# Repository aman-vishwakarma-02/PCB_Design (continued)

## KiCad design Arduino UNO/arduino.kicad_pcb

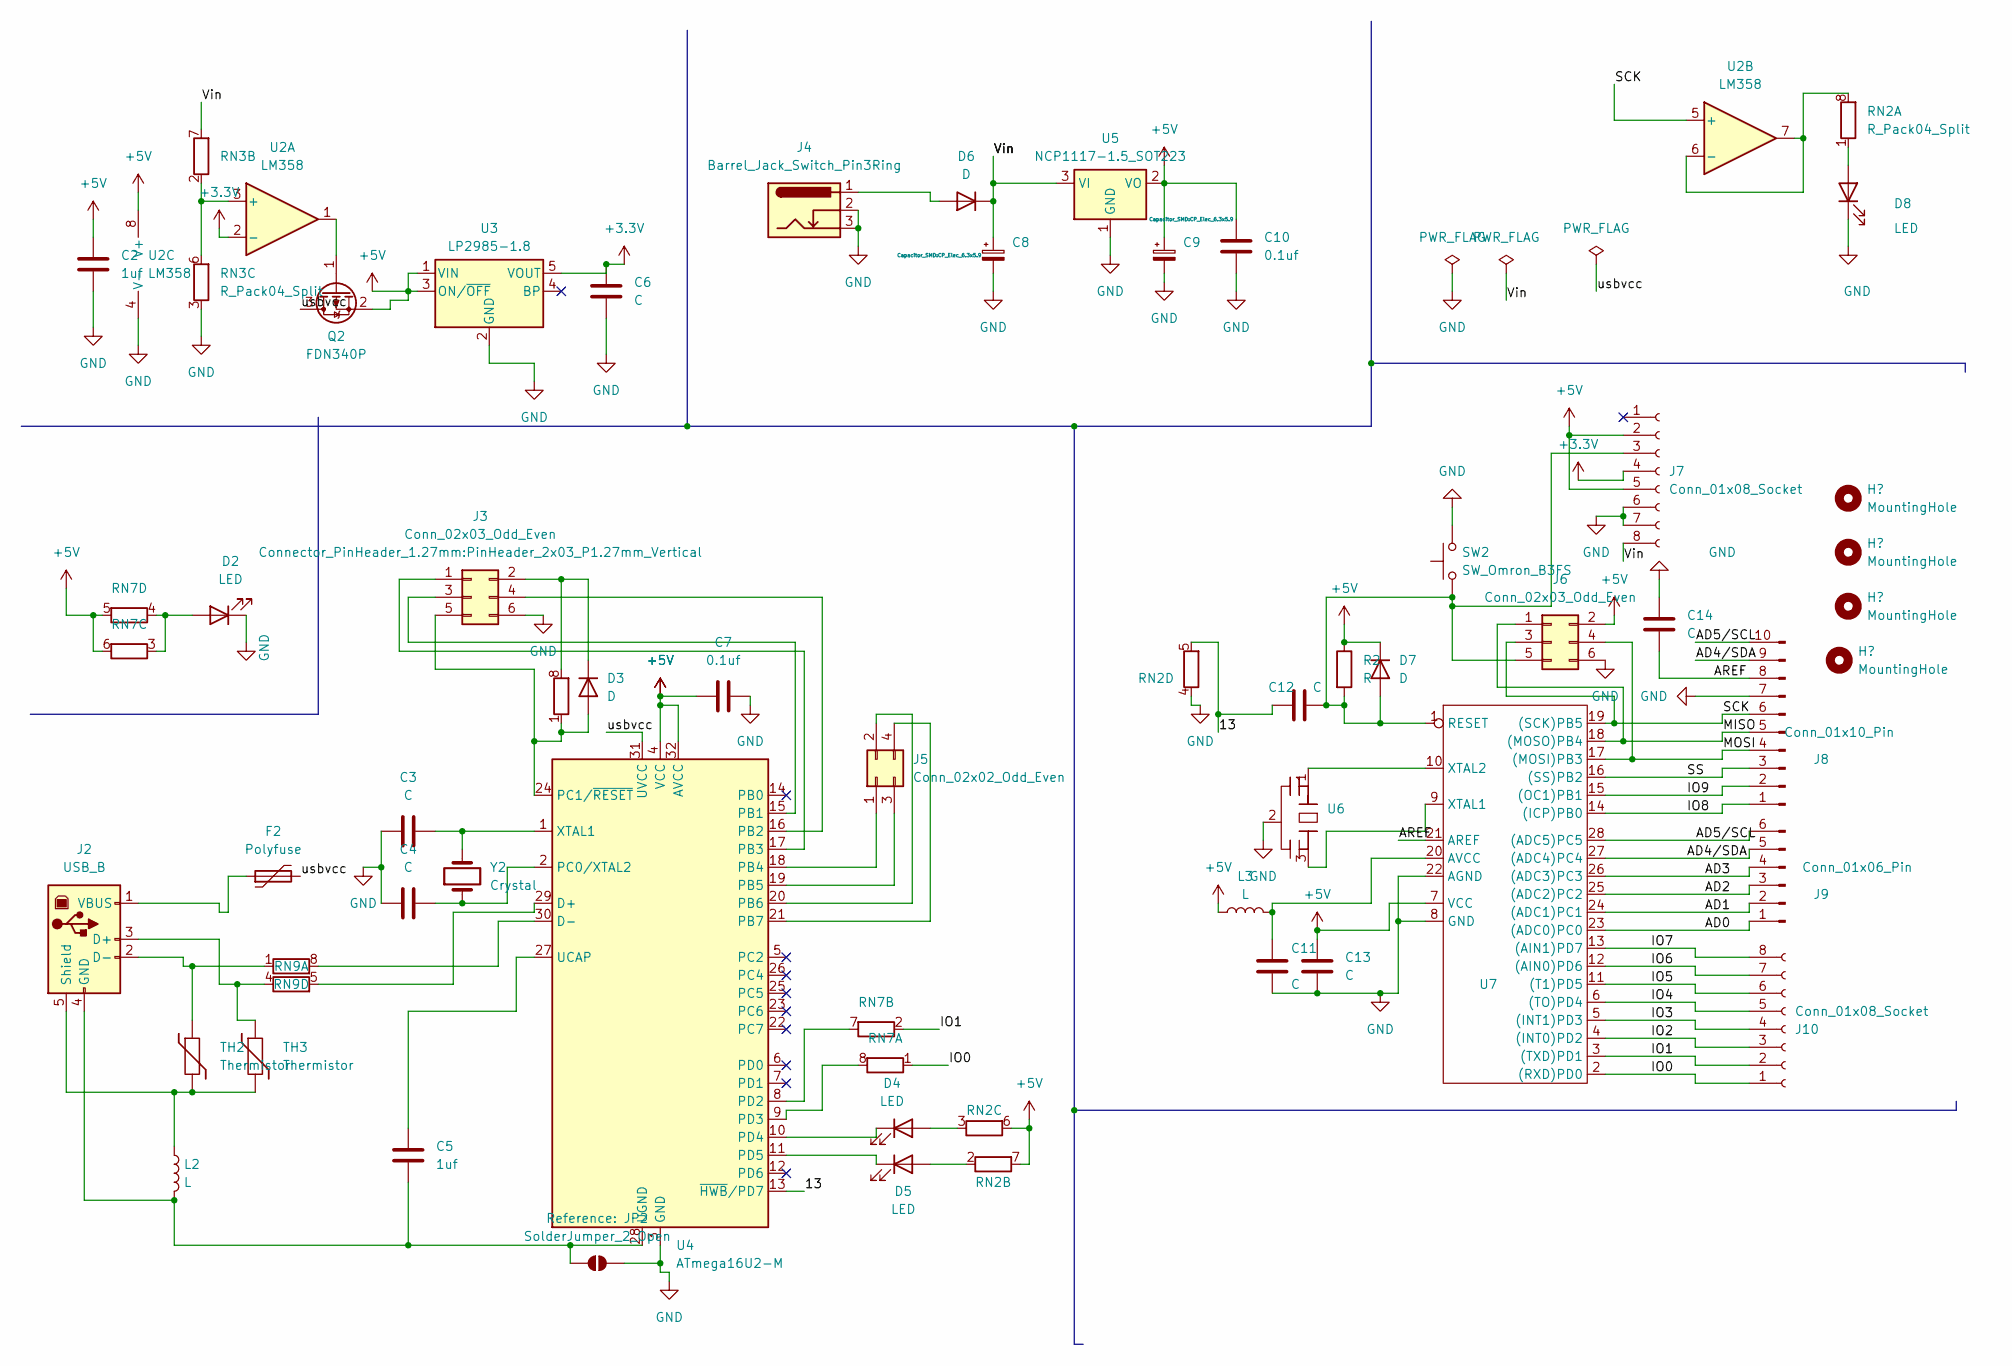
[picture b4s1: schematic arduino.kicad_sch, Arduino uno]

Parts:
C2, C5: 1uf; C_0603_1608Metric
C3, C4: C; C_0603_1608Metric_Pad1.08x0.95mm_HandSolder
C6: C; C_0805_2012Metric
C7, C10: 0.1uf; C_0603_1608Metric
C8, C9: C_Polarized_Small; CP_Elec_6.3x5.9
C11, C12, C13, C14: C; C_0603_1608Metric
D2, D4, D5: LED; LED_0402_1005Metric_Pad0.77x0.64mm_HandSolder
D3: D; D_0805_2012Metric_Pad1.15x1.40mm_HandSolder
D6: D; D_SOD-523
D7: D; D_1206_3216Metric_Pad1.42x1.75mm_HandSolder
D8: LED; LED_0603_1608Metric
F2: Polyfuse; R_1812_4532Metric
J2: USB_B; USB_B_OST_USB-B1HSxx_Horizontal
J3, J6: Conn_02x03_Odd_Even; PinHeader_2x03_P1.27mm_Vertical
J4: Barrel_Jack_Switch_Pin3Ring; BarrelJack_Wuerth_6941xx301002
J5: Conn_02x02_Odd_Even; PinHeader_2x02_P1.27mm_Vertical
J7, J10: Conn_01x08_Socket; PinSocket_1x08_P2.54mm_Vertical
J8: Conn_01x10_Pin; PinSocket_1x10_P2.54mm_Vertical
J9: Conn_01x06_Pin; PinSocket_1x06_P2.54mm_Vertical
JP2: SolderJumper_2_Open; SolderJumper-2_P1.3mm_Open_Pad1.0x1.5mm
L2: L; L_0603_1608Metric
L3: L; L_0805_2012Metric
Q2: FDN340P; SOT-23
R2: R; R_0603_1608Metric
RN2, RN9D2: R_Pack04_Split; R_Array_Convex_4x0402
RN3, RN7, RN9: R_Pack04_Split; R_Array_Concave_4x0402
SW2: SW_Omron_B3FS; SW_SPST_Omron_B3FS-100xP
TH2, TH3: Thermistor; R_0201_0603Metric
U2: LM358; SOIC-8_3.9x4.9mm_P1.27mm
U3: LP2985-1.8; SOT-23-5
U4: ATmega16U2-M; QFN-32-1EP_5x5mm_P0.5mm_EP3.3x3.3mm
U5: NCP1117-1.5_SOT223; SOT-223-3_TabPin2
U6: CSTCE16M0V53-R0
U7: DIP-28_W7.62mm_LongPads
Y2: Crystal; Crystal_HC49-4H_Vertical

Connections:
+3.3V: C6.1, J7.4, U2.2 (-), U3.5 (VOUT)
+5V: C2.2, C7.1, C9.1, C10.1, C13.2, D7.1 (K), J6.2, J7.2, J7.5, L3.1, Q2.2 (S), R2.1, RN2.6 (R3.2), RN2.7 (R2.2), RN7.5 (R4.2), RN7.6 (R3.2), U2.8 (V+), U3.1 (VIN), U3.3 (ON/~OFF), U4.4 (VCC), U4.32 (AVCC), U5.2 (VO), U7.7 (VCC); also elsewhere on the board
/13: C12.1, RN2.5 (R4.2), U4.13 (~HWB/PD7)
/AD0: J9.1, U7.23 ((ADC0)PC0)
/AD1: J9.2, U7.24 ((ADC1)PC1)
/AD2: J9.3, U7.25 ((ADC2)PC2)
/AD3: J9.4, U7.26 ((ADC3)PC3)
/AD4/SDA: J8.9, J9.5, U7.27 ((ADC4)PC4)
/AD5/SCL: J8.10, J9.6, U7.28 ((ADC5)PC5)
/AREF: C14.1, J8.8, U7.21 (AREF)
/IO0: J10.1, RN7.1 (R1.1), U7.2 ((RXD)PD0); also elsewhere on the board
/IO1: J10.2, RN7.2 (R2.1), U7.3 ((TXD)PD1); also elsewhere on the board
/IO2: J10.3, U7.4 ((INT0)PD2)
/IO3: J10.4, U7.5 ((INT1)PD3)
/IO4: J10.5, U7.6 ((TO)PD4)
/IO5: J10.6, U7.11 ((T1)PD5)
/IO6: J10.7, U7.12 ((AIN0)PD6)
/IO7: J10.8, U7.13 ((AIN1)PD7)
/IO8: J8.1, U7.14 ((ICP)PB0)
/IO9: J8.2, U7.15 ((OC1)PB1)
/MISO: J6.1, J8.5, U7.18 ((MOSO)PB4)
/MOSI: J6.4, J8.4, U7.17 ((MOSI)PB3)
/SCK: J6.3, J8.6, U2.5 (+), U7.19 ((SCK)PB5)
/SS: J8.3, U7.16 ((SS)PB2)
/Vin: C8.1, D6.1 (K), J7.8, RN3.7 (R2.2), U5.3 (VI)
/usbvcc: F2.2, Q2.3 (D), U4.31 (UVCC)
GND: C2.1, C3.1, C4.1, C6.2, C7.2, C8.2, C9.2, C10.2, C11.2, C13.1, C14.2, D2.1 (K), D8.1 (K), J3.6, J4.2, J4.3, J6.6, J7.6, J7.7, J8.7, JP2.2 (B), RN2.4 (R4.1), RN3.3 (R3.1), SW2.2, U2.4 (V-), U3.2 (GND), U4.3 (GND), U4.33 (GND), U5.1 (GND), U6.2, U7.8 (GND), U7.22 (AGND)
unnamed 27: D2.2 (A), RN7.3 (R3.1), RN7.4 (R4.1); also elsewhere on the board
unnamed: D3.2 (A), J3.5, RN9D2.1 (R1.1), U4.24 (PC1/~RESET)
unnamed: D3.1 (K), J3.2, RN9D2.8 (R1.2)
unnamed: D4.2 (A), RN2.3 (R3.1)
unnamed: D4.1 (K), U4.10 (PD4)
unnamed: D5.2 (A), RN2.2 (R2.1)
unnamed: D5.1 (K), U4.11 (PD5)
unnamed: D6.2 (A), J4.1
unnamed: C12.2, D7.2 (A), J6.5, J7.3, R2.2, SW2.1, U7.1 (RESET)
unnamed: D8.2 (A), RN2.1 (R1.1)
unnamed: J2.3 (D+), RN9.4 (R4.1), TH3.1
unnamed: J2.2 (D-), RN9.1 (R1.1), TH2.1
unnamed: C5.2, J2.4 (GND), JP2.1 (A), L2.2, U4.28 (UGND)
unnamed: J2.5 (Shield), L2.1, TH2.2, TH3.2
unnamed: F2.1, J2.1 (VBUS)
unnamed: J3.1, U4.17 (PB3)
unnamed: J3.3, U4.15 (PB1)
unnamed: J3.4, U4.16 (PB2)
unnamed: J5.1, U4.18 (PB4)
unnamed: J5.2, U4.20 (PB6)
unnamed: J5.3, U4.19 (PB5)
unnamed: J5.4, U4.21 (PB7)
unnamed: Q2.1 (G), U2.1
unnamed: RN2.8 (R1.2), U2.6 (-), U2.7
unnamed: RN3.2 (R2.1), RN3.6 (R3.2), U2.3 (+)
unnamed 52: RN7.8 (R1.2), U4.9 (PD3); also elsewhere on the board
unnamed 53: RN7.7 (R2.2), U4.8 (PD2); also elsewhere on the board
unnamed: RN9.8 (R1.2), U4.30 (D-)
unnamed: RN9.5 (R4.2), U4.29 (D+)
unnamed: C4.2, U4.2 (PC0/XTAL2), Y2.1
unnamed: C5.1, U4.27 (UCAP)
unnamed: C3.2, U4.1 (XTAL1), Y2.2
unnamed: C11.1, L3.2, U7.20 (AVCC)
unnamed: U6.3, U7.9 (XTAL1)
unnamed: U6.1, U7.10 (XTAL2)

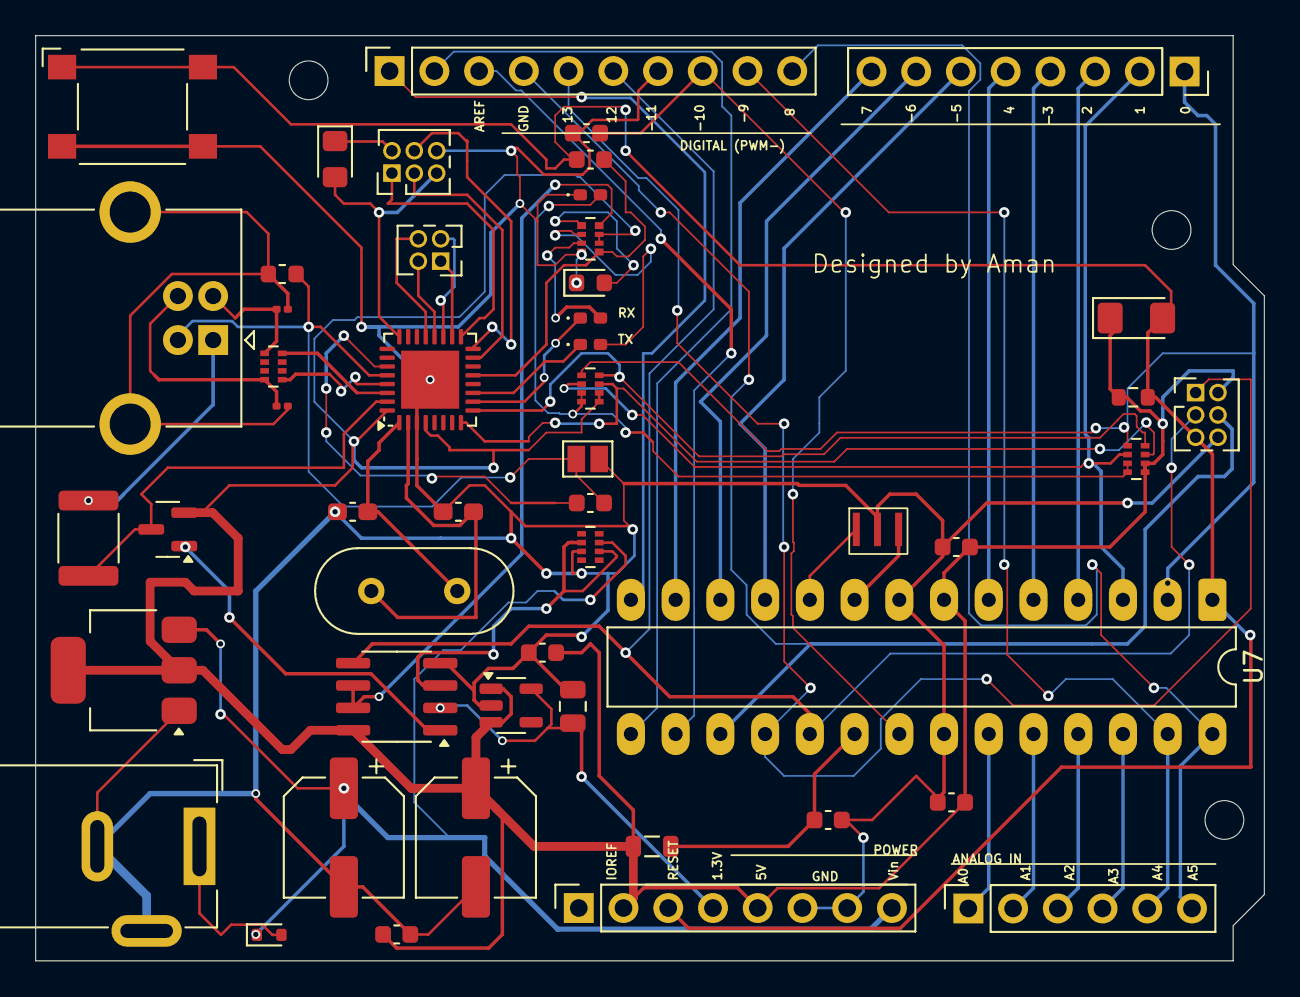
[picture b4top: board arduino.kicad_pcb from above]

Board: 2 copper layers, 69.8 x 52.5 mm, 50 parts (0 on the bottom side), 62 nets.

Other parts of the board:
RN7#2: R_Pack04_Split; R_Array_Concave_4x0402

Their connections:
+5V: RN7#2.5 (R4.2), RN7#2.6 (R3.2); also elsewhere on the board
/IO0: RN7#2.1 (R1.1); also elsewhere on the board
/IO1: RN7#2.2 (R2.1); also elsewhere on the board
unnamed 27: RN7#2.3 (R3.1), RN7#2.4 (R4.1); also elsewhere on the board
unnamed 52: RN7#2.8 (R1.2); also elsewhere on the board
unnamed 53: RN7#2.7 (R2.2); also elsewhere on the board

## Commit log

2025-09-02 Initial commit: PCB design Projects
2025-09-05 My PCB design
2025-10-16 add files
